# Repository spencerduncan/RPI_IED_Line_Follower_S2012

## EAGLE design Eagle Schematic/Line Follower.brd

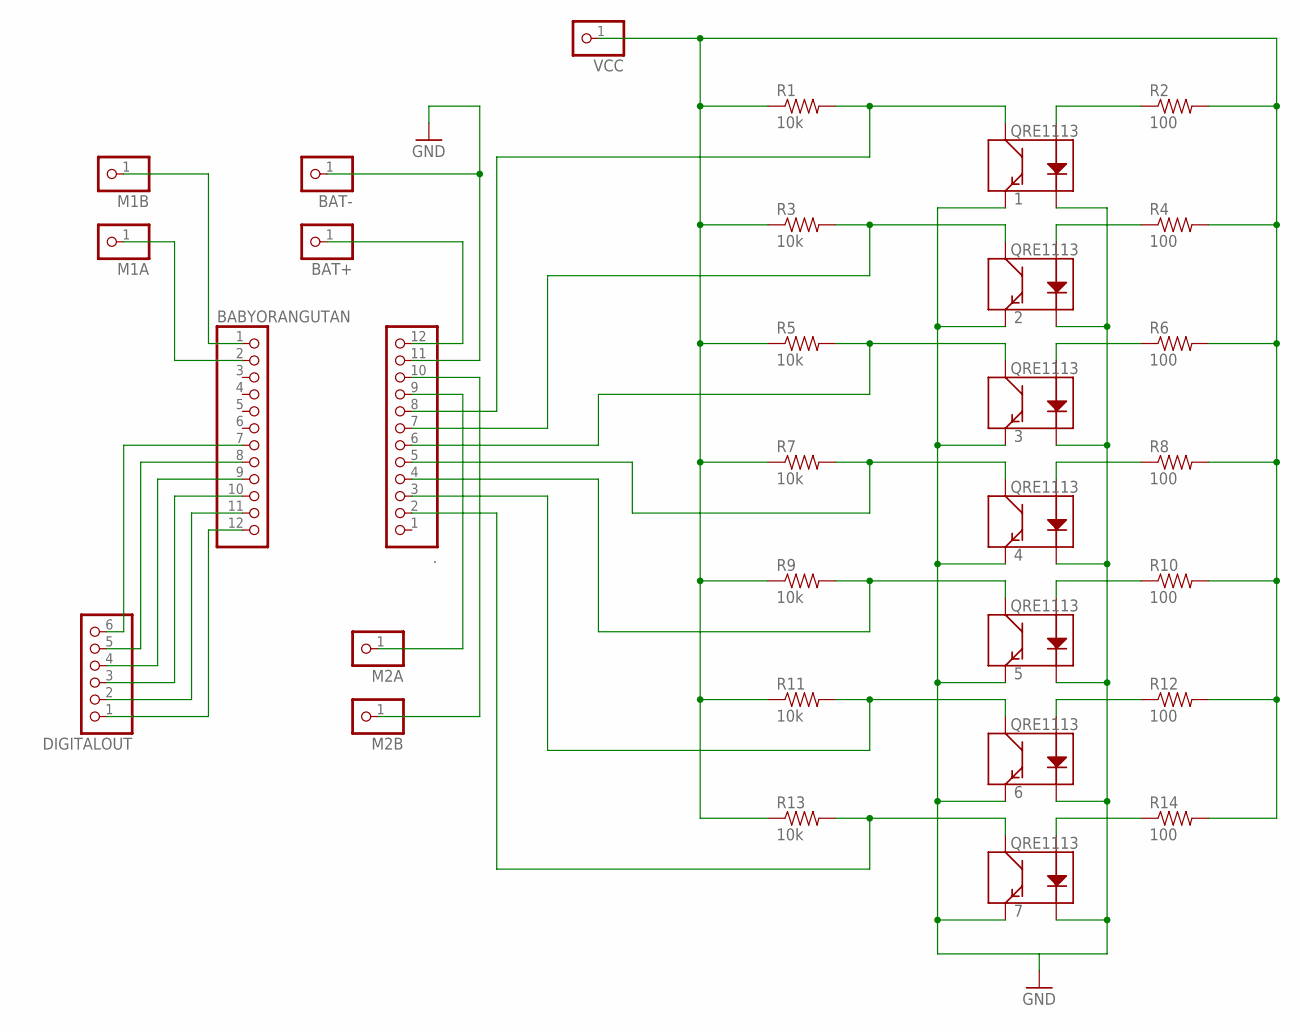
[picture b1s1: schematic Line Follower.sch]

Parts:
1, 2, 3, 4, 5, 6, 7: QRE1113
.: PINHD-1X12; 1X12
BABYORANGUTAN: PINHD-1X12; 1X12
BAT+: PINHD-1X1; 1X01
BAT-: PINHD-1X1; 1X01
DIGITALOUT: PINHD-1X6; 1X06
M1A, M1B, M2A, M2B: PINHD-1X1; 1X01
R1, R3, R5, R7, R9, R11, R13: 10k; 0603-RES
R2, R4, R6, R8, R10, R12, R14: 100; 0805
VCC: PINHD-1X1; 1X01

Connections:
GND: 1.2 (K), 1.4 (E), 2.2 (K), 2.4 (E), 3.2 (K), 3.4 (E), 4.2 (K), 4.4 (E), 5.2 (K), 5.4 (E), 6.2 (K), 6.4 (E), 7.2 (K), 7.4 (E), ..11, BAT-.1
unnamed: 1.3 (C), ..8, R1.2
unnamed: 4.3 (C), ..5, R7.2
unnamed: ..12, BAT+.1
unnamed: BABYORANGUTAN.7, DIGITALOUT.6
unnamed: BABYORANGUTAN.8, DIGITALOUT.5
unnamed: 1.1 (A), R2.1
unnamed: 2.1 (A), R4.1
unnamed: 3.1 (A), R6.1
unnamed: 4.1 (A), R8.1
unnamed: 5.1 (A), R10.1
unnamed: 6.1 (A), R12.1
unnamed: 7.1 (A), R14.1
unnamed: R1.1, R2.2, R3.1, R4.2, R5.1, R6.2, R7.1, R8.2, R9.1, R10.2, R11.1, R12.2, R13.1, R14.2, VCC.1
unnamed: BABYORANGUTAN.9, DIGITALOUT.4
unnamed: BABYORANGUTAN.10, DIGITALOUT.3
unnamed: 2.3 (C), ..7, R3.2
unnamed: BABYORANGUTAN.11, DIGITALOUT.2
unnamed: BABYORANGUTAN.12, DIGITALOUT.1
unnamed: 3.3 (C), ..6, R5.2
unnamed: BABYORANGUTAN.1, M1B.1
unnamed: BABYORANGUTAN.2, M1A.1
unnamed: ..9, M2A.1
unnamed: ..10, M2B.1
unnamed: 5.3 (C), ..4, R9.2
unnamed: 6.3 (C), ..3, R11.2
unnamed: 7.3 (C), ..2, R13.2

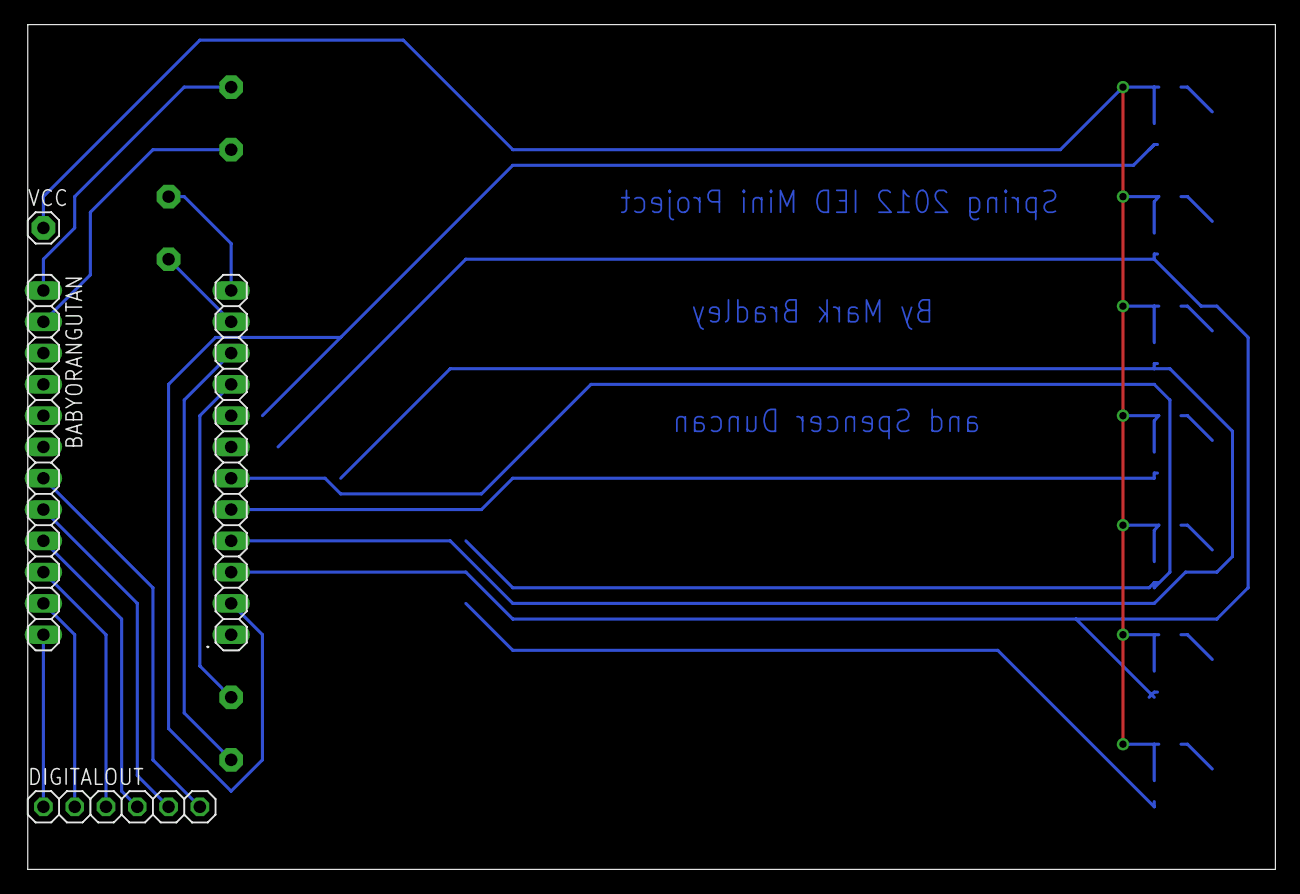
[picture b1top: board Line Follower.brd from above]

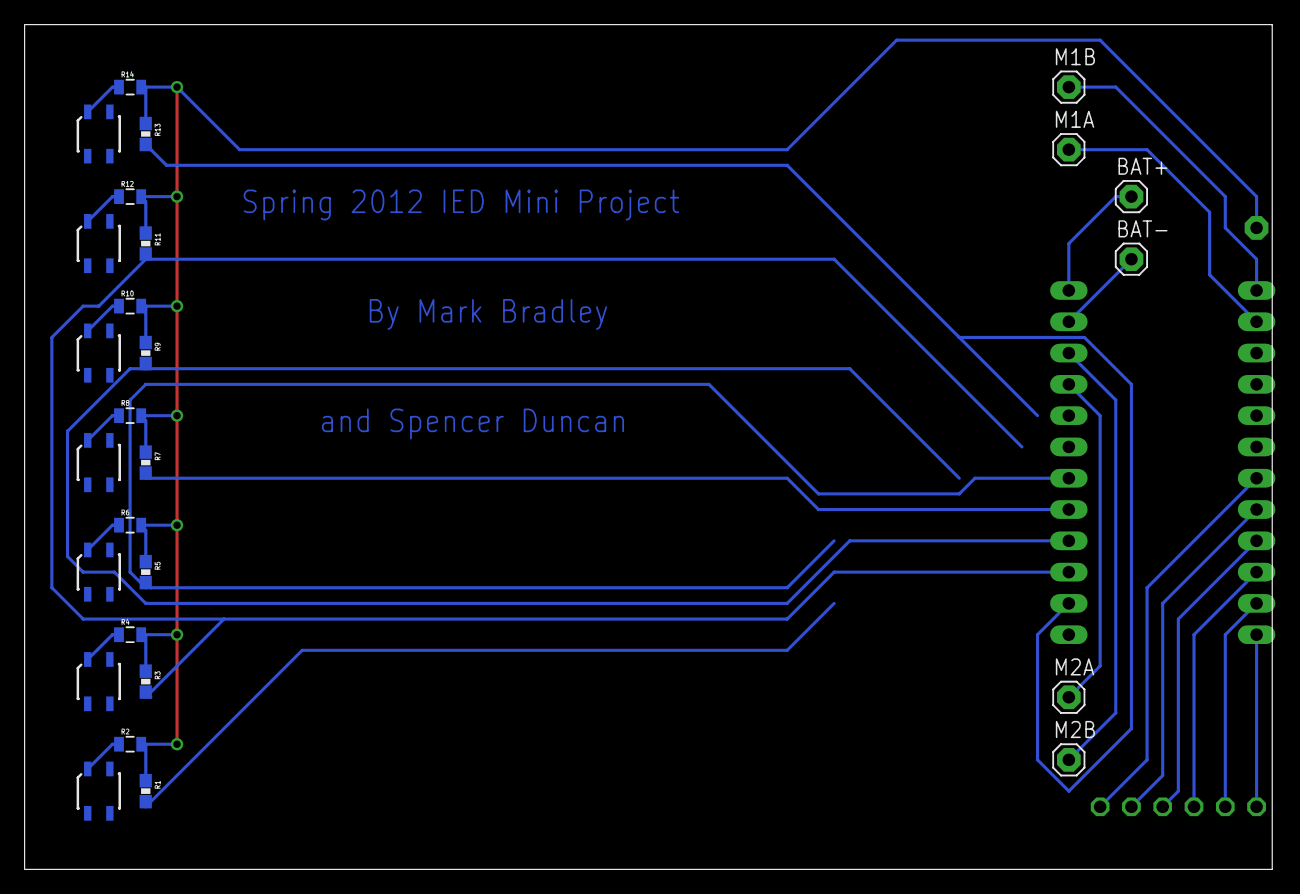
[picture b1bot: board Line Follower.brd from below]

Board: 2 copper layers, 101.3 x 68.6 mm, 31 parts (27 on the bottom side), 27 nets.

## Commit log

2014-02-12 Commit From Archive
    Best of luck to ye, merry reader!

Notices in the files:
parts and their libraries:
SparkFun: Licensing: CC v3.0 Share-Alike You are welcome to use this library for commercial purposes.
